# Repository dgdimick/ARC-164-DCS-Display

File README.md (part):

# ARC-164 Radio Panel for DCS

**Last updated: November 14, 2026 at 2:04 AM MST (America/Denver)**

**[Windows COM port tools](Tools/README.md)** — Download the scripts to rename a COM port in Device Manager or restore its previous display name.

*Panel reference photo: PC Flights.*

I’m building an ARC-164 radio panel for my SIMPIT and sharing the files and what I learn along the way. I hope you’ll enjoy building one too, and perhaps help me make it better.

I spend about **8 hours a day on my SIMPIT projects**, including working on the code, PCB design, assembly, and test fitting.

## Development update — November 14, 2026

I finished all three ARC-164 PCB designs and published them as prototypes. The set includes **Main Board v1.2**, **LED Sub Board v1.2**, and **Power Driver Board v1.0**. Next I’ll assemble the manufactured boards and test them electrically. [View the PCB files and downloads](PCBs/README.md).

## Development update — November 10, 2026

**LED Sub Board v1.2 is now published for Main Board v1.2.** I printed the latest mockup at **100%** and it passed the fit test, including **frequency and channel LED alignment and J20 connector/cable clearance**. The final layout keeps the **FREQ LEDs up 0.5 mm**, the **channel LEDs up 0.5 mm with their earlier 0.5 mm leftward adjustment**, and **J20 up 2 mm total** from the previous mounting position. The **0.75 mm gaps, 6 mm display bodies and tested 8 mm mounting stack** remain unchanged. **Use Main Board v1.2 with LED Sub Board v1.2; older Sub Boards do not match this Main Board. Assembled electrical testing is still pending.** [Download the Sub Board v1.2 files and tested STL](PCBs/v1.2/LED-Subboard/README.md).

[Read previous development updates](Docs/Development-Updates.md).

## Physical mockup — November 6, 2026

Here’s my current ARC-164 mockup, showing the faceplate, control shafts, and display covers together with the 3D-printed board assembly. I’m using this to check the mechanical layout and clearances as I continue building the encoder version. This is a physical mockup, not a completed or electrically tested panel. Click the photo to see it full size.

## Power Board images

### Front of the Power Board

Click the image to view it full size.

## Main Board images

### Front of the Main Board

### Back of the Main Board

Click either image to view it full size.

## PCB Sub-Board images

These images show the earlier Sub Board layout, which **does not match Main Board v1.2**. Use the [current Sub Board v1.2 files and tested mockup](PCBs/v1.2/LED-Subboard/README.md) for the matching layout.

### Front of the PCB Sub-Board

### Back of the PCB Sub-Board

Click either image to view it full size.

## Current development order

I’ll **finish the ARC-164 PCBs**, then **take a break from design work and go back to testing the ARC-210**. **The ARC-186 and Version 2 plans can wait.** I haven’t set a date to return to those designs or additional aircraft support.

**This order may change based on user feedback and interest.** These are plans, not fixed release dates.

### Future versions and upgrades

**Future upgrades:** It may be as long as **two years** before I return to this project with upgrades or a new version. Please treat future-version ideas as long-term plans, with no promised release date.

## Other SIMPIT panels

Once I’ve finished the radio panels, I plan to build other panels for my SIMPIT, including the **SAS and emergency trim panels**. I’ll share those projects as they develop. These are future plans.

## Through-hole components

While I could use surface-mount (SMD) parts to make the boards smaller, I plan to use through-hole components to make the project easier for everyone to build and solder with basic tools.

I’ve linked the parts I’m designing around so you can find the same sizes and pin spacing without having to hunt through listings. You’re welcome to use other suppliers—I buy some parts from Amazon myself. Just compare the dimensions and pin spacing before ordering a substitute so it will fit the PCB.

## Recorded component costs

These are my recorded purchases so far, in **US dollars**. The total includes rotary switches bought before I returned to frequency encoders; it is not a shopping list for the current design. The **A11015RNCQ switches are 10-position switches** and were the wrong parts for the ARC-164. **DigiKey did not cancel my order, so I’ll keep the A11015RNCQ switches as parts for ARC-210 V2**.

| Item | Quantity | Cost (USD) |
|---|---:|---:|
| QBSLDIW301GR white seven-segment LED digits — earlier purchase; superseded by SC36-11SURKWA in the current build plan | 10 | $17.43 |
| A12515RNCQ rotary switches — earlier long-shaft selection; no longer the current MAIN/PRESET choice | 5 | $55.66 |
| A11015RNCQ rotary switches — 10 positions; DigiKey order not canceled, retained for ARC-210 V2 | 3 | $35.07 |
| Tax and tariffs on the rotary-switch and LED order | — | $27.13 |
| Toggle-switch purchase | — | $13.51 |
| Toggle-switch purchase | — | $10.76 |
| Faceplate | 1 | $57.00 |
| Faceplate shipping | — | $13.59 |
| Pushbutton switches | — | $7.99 |
| Teensy 4.1 | 1 | $29.60 |
| Teensy shipping | — | $8.35 |
| **Running total** | | **$276.09** |

My Teensy 4.1 cost **$37.95 including shipping**, and my faceplate cost **$70.59 including shipping**. The rotary switches and LEDs came to **$108.16**, or **$135.29 including tax and tariffs**. Those charges are already included in the running total. I bought two spare LED digits and one spare A12515RNCQ switch because the quantity price breaks saved me money compared with buying only the quantities I originally planned to use. I still need to verify the selected toggle switches’ fit and operation.

I’m keeping the extra displays I bought as spares, since returning them would only get me **US$2.77** back.

**The VOL encoder isn’t included in the total yet.** My current selection for VOL, FREQ, and channel is **PEC11R-4230F-S0024 with a 30 mm shaft**, sourced from Mouser. I’ll add actual encoder costs to this purchase history once the order is confirmed.

**This total is before PCBs, display drivers, resistors, connectors, and the other remaining parts. It is not the complete build cost.** I’ll update the total as I buy the remaining parts. Additional shipping or fees not listed above are also excluded.

## Order sheet — rotary controls and LED digits

**Current build: rotary encoders.** I’ll finish the current ARC-164 PCBs, then take a break from design work and return to testing the ARC-210. The ARC-186 and Version 2 rotary-switch plans are deferred; PC Flights has confirmed the larger-hole panel is available on request when I’m ready for it. The order sheet below is for the encoder version; quantities and fit still need final checks before purchasing.

This is my order sheet for **one ARC-164 panel**, updated **November 4, 2026**. I’ll buy the **30 mm encoders and SC36-11SURKWA LED digits from Mouser**. The MAIN and PRESET switches remain on the DigiKey list. These are full build quantities; I’ll deduct parts I already have before ordering.

| Quantity | Use | Manufacturer part number | Supplier / order number | Estimated unit price (USD) | Estimated total (USD) |
| ---: | --- | --- | --- | ---: | ---: |
| 7 | Five FREQ encoders, channel encoder, and VOL | PEC11R-4230F-S0024 | [Mouser: 652-PEC11R-4230F-S24](https://www.mouser.com/en/ProductDetail/Bourns/PEC11R-4230F-S0024?qs=Zq5ylnUbLm6MC5h%2FLr6Brg%3D%3D) | $2.07 | $14.49 |
| 2 | MAIN and PRESET rotary switches | A12505RNCQ | [DigiKey: CKN10203-ND](https://www.digikey.com/en/products/detail/c-k/A12505RNCQ/2043159) | $13.41 | $26.82 |
| 10 | Red 0.36-inch common-cathode seven-segment LED digits | SC36-11SURKWA | [Mouser: 604-SC36-11SURKWA](https://www.mouser.com/en/ProductDetail/Kingbright/SC36-11SURKWA?qs=FRBiz4Wv1YMkVf5BvlPtDA%3D%3D) | $1.45 | $14.50 |
| | **Estimated subtotal** | | | | **$55.81** |

All seven encoders have **30 mm shafts**. MAIN and PRESET use the **same A12505RNCQ switch**, with the stop ring set to **4 positions for MAIN** and **3 positions for PRESET**; both index at **45° per position**.

This earlier estimate uses the quantity-five encoder tier, quantity-one switch tier, and Mouser’s quantity-ten SC36-11SURKWA LED tier; it has not yet been recalculated for my purchased white displays. The LED price is $1.45 each ($14.50 for ten), checked November 4, 2026. Prices can change; shipping, tax, and tariffs are excluded. This estimate is separate from my recorded purchases.

**This is not the complete build BOM.** TONE, SQL, STATUS, display drivers, other display components, resistors, capacitors, connectors, PCBs, and other remaining parts are excluded.

### Recommended IC sockets and Teensy headers

**I normally recommend using sockets for the DIP ICs and a removable header/socket connection for the Teensy.** This reduces the risk of overheating the ICs when soldering and makes replacement easier. Solder the empty sockets to the PCB first, let the board cool, and then insert the ICs with their pin-1 notches facing the correct way.

| Quantity | Use | Manufacturer part number | Mouser order number / link |
| ---: | --- | --- | --- |
| 2 | 24-pin DIP sockets for the MAX7219 drivers, U11 and U12; 7.62 mm row spacing, 2.54 mm pin pitch | TE Connectivity 1-2199298-8 | [571-1-2199298-8](https://www.mouser.com/ProductDetail/TE-Connectivity/1-2199298-8?qs=fK8dlpkaUMsSY7Gqcrol0Q%3D%3D) |
| 1 | 14-pin DIP socket for the 74AHCT125 buffer, U13; 7.62 mm row spacing, 2.54 mm pin pitch | TE Connectivity 1-2199298-3 | [571-1-2199298-3](https://www.mouser.com/en/ProductDetail/TE-Connectivity/1-2199298-3?qs=fK8dlpkaUMtBOtVI99wRlQ%3D%3D) |
| 2 | Single-row 24-pin male headers for the Teensy 4.1's two outer rows; 2.54 mm pitch | Samtec TSW-124-07-T-S | [200-TSW12407TS](https://www.mouser.com/en/ProductDetail/Samtec/TSW-124-07-T-S?qs=rU5fayqh%252BE26VY6qw728rQ%3D%3D) |
| 2 | Matching single-row 24-pin female sockets on the Power Driver Board; 2.54 mm pitch | Samtec SSW-124-01-T-S | [200-SSW12401TS](https://www.mouser.com/ProductDetail/Samtec/SSW-124-01-T-S?qs=iT52DjcXudvCUishYlzKnw%3D%3D) |

All of these parts are through-hole and can be hand soldered. The Teensy still needs its male headers soldered on unless you buy it with pins already fitted; use a temperature-controlled iron and avoid prolonged heating. The female sockets let you unplug the complete Teensy module from the Power Driver Board. Check the added socket/header height when setting the clearance to the board above it. These items are separate from the rotary-control and LED subtotal; check current supplier pricing.

### External regulated 5 V power supply

| Quantity | Use | Manufacturer part number | Supplier / order number |
| ---: | --- | --- | --- |
| 1 | J11 edge-mounted, right-angle, through-hole barrel power jack | Same Sky PJ-102AH | [Mouser: 490-PJ-102AH](https://www.mouser.com/en/ProductDetail/Same-Sky/PJ-102AH?qs=WyjlAZoYn50Yq4CrVLCXLw%3D%3D) |
| 1 | Regulated 5 V, 4 A supply for the displays and panel backlighting | MEAN WELL GST25A05-P1J | [Mouser: 709-GST25A05-P1J](https://www.mouser.com/en/ProductDetail/MEAN-WELL/GST25A05-P1J?mgh=1&qs=drgMNd%252BkGPOX8brSXUPVtQ%3D%3D) |

**You can use another power supply, but it must provide well-regulated 5 V DC**, with a voltage tolerance of **±5% or better**, enough current for the connected panels, and a **5.5 mm outer / 2.1 mm inner, center-positive barrel plug** to fit J11. The recommended supply provides 4 A; the circuit draws only the current it needs. The Power Driver Board does not reduce a higher input voltage to 5 V.

The GST25A05-P1J requires a separate **IEC C13 mains cord** (the standard desktop-computer type). See the [MEAN WELL datasheet](https://www.meanwell.com/Upload/PDF/GST25A/GST25A-SPEC.PDF). The Teensy remains powered through USB; the external supply powers the display and backlight circuits. The jack, supply, and mains cord are **not included in the rotary-control and LED subtotal above**; check current supplier pricing.

### USB adapter cable

Use **one USB-C-to-Micro-B data cable per panel** to connect the Teensy 4.1’s Micro-B device port to a computer or hub with a USB-C port. The linked option is a **1 ft (30.5 cm), male-to-male cable carrying both data and power**:

[Amazon — USB-C-to-Micro-B adapter cable](https://www.amazon.com/dp/B0BD36TZBK)

This replaces the standard USB Micro-B data cable when using a USB-C port; you only need one suitable USB data cable per panel. A charge-only cable will not carry DCS-BIOS communications or program the Teensy. Choose a length that suits your installation and check the current supplier price.

The USB cable is separate from the rotary-control and LED subtotal above; its cost has not been added to the recorded purchase history.

### Additional Mouser items — green panel backlighting

I’ve selected **Kingbright WP710A10SGD**, a **3 mm through-hole green LED with a diffused lens**, for the ARC-164 and ARC-210 panel-backlighting plan. See [Mouser part 604-WP710A10SGD](https://www.mouser.com/ProductDetail/Kingbright/WP710A10SGD?qs=jBF9H7RTBaS5vBvRdVQZww%3D%3D) and the [Kingbright datasheet](https://www.kingbrightusa.com/images/catalog/spec/wp710a10sgd.pdf). Final brightness, light spread, and mounting fit behind the lettering still need testing.

**Backlight LED quantities are still being decided.** The figures below are provisional planning estimates, not finalized purchase quantities. I’ll confirm them after laying out the LEDs behind the lettering and testing light coverage.

| Provisional quantity | Allocation | Manufacturer part number | Mouser order number |
| ---: | --- | --- | --- |
| 19 | ARC-164 Version 1.0 prototype backlighting | WP710A10SGD | 604-WP710A10SGD |
| 38 | ARC-210 backlighting | WP710A10SGD | 604-WP710A10SGD |
| **57 total** | **Planning total only; final quantity TBD, excluding spares** | **WP710A10SGD** | **604-WP710A10SGD** |

These LEDs require **one current-limiting resistor per LED branch** on the regulated 5 V supply. I’ll start brightness testing with **330 Ω resistors**, approximately **8.5 mA per LED** at the datasheet’s typical 2.2 V forward voltage; actual current and brightness will vary. For the provisional 57-LED combined estimate, that nominal current would draw approximately 0.48 A at full duty, excluding the displays and controllers. The final resistor selection and power budget remain subject to testing.

The LEDs will sit behind the lettering, with opaque shielding around display windows. They will use the panel-backlighting driver, not the MAX7219 segment outputs. **Confirm price and availability in the Mouser cart; these additional LEDs and their resistors are not included in the $55.81 ARC-164 subtotal above.**

### Additional item for my Mouser order — emergency trim panel

I’ll add this part to the same Mouser order as the ARC-164 encoders. It is for my **A-10 emergency pitch/roll trim panel**, not the ARC-164 radio.

| Quantity | Use | Manufacturer part number | Mouser order number | Estimated cost (USD) |
| ---: | --- | --- | --- | --- |
| 1 | Emergency pitch/roll trim directional switch | Alps Alpine RKJXT1F42001 | [688-RKJXT1F42001](https://www.mouser.com/en/ProductDetail/Alps-Alpine/RKJXT1F42001?qs=6EGMNY9ZYDTsBzSTrhiL0w%3D%3D) | Confirm USD price in cart |

This is a **four-direction switch with a center pushbutton and rotary encoder**. I plan to use its four directions for emergency pitch and roll trim; the center pushbutton and rotary encoder will remain unused. Physical mounting, knob fit, and operating feel still need checking. Its cost is **not included in the $55.81 ARC-164 subtotal** above.

## 3D print settings

Use a **0.20 mm or finer layer height**. Print the knobs **without supports** in their intended orientation.

The rotary encoder shaft adapters will be hidden. Black filament is preferred if you have it available.

## Free 3D-printed parts

If you don’t have a 3D printer, I’m happy to help with the ARC-164. Once the printed parts are finalized, I’ll print a set for you for free. Just cover shipping. I’m still designing and test-fitting some of the printed parts. If you’re planning a build, [get in touch in Discussions](https://github.com/dgdimick/ARC-164-DCS-Display/discussions) to check availability.

## Things that need to be completed

**Last updated: November 11, 2026 at 10:50 PM MST (America/Denver)**
<!-- Refresh this section timestamp whenever the work list changes, using the actual America/Denver time and MST/MDT. -->

This is my current work list for the hardware, firmware, testing, and build instructions.

1. **Panel layout and parts:** Confirm dimensions, mounting clearances, controls, and the complete parts list. **TONE and SQL switches:** Select the exact parts and verify their mounting dimensions, required operation and travel, and clearances before finalizing the PCB. My purchased **QBSLDIW301GR white digits—six for frequency and two for channel—have passed the printed layout fit test**. The revised six-digit frequency layout is **49.35 mm wide × 13.75 mm high across the front face**, using **0.75 mm gaps**. The earlier LED layout mockup passed at 100% scale; the matching **Sub Board v1.2 has now passed its latest frequency/channel LED alignment and J20 clearance fit checks and is published**. Verify the prototype LED Sub-Board footprint and pinout against these displays before assembly. Check digit visibility and brightness through the smoked covers, pinout, mounting height, spacing, and clearance within the 53.5 × 17.5 mm frequency window and 22 × 17.5 mm preset window.
2. **Assemble and electrically test the matched v1.2 boards:** The **LED Sub Board v1.2 mockup passed its 100% print and fit test on November 10, 2026**, including frequency/channel LED alignment and J20 connector/cable clearance with Main Board v1.2. Both boards are published. Verify the manufactured boards, connector/cable fit, power, display pinout, controls and assembled electrical operation before calling the complete panel tested. Keep the current frequency-encoder design; I’ll finish these PCBs and return to ARC-210 testing before revisiting ARC-186 or Version 2.
3. **Printed parts:** The **8 mm Sub Board mounting stack** and **latest v1.2 display-board mockup** have passed physical fit testing at **100% scale**, including both display windows and J20 clearance. Continue designing and test-fitting the remaining knobs, brackets and spacers; verify shaft engagement, knob retention and their clearances. Design and test-fit shaft adapters for the rotary encoders.
4. **DCS-BIOS mappings and any needed changes:** Check which inputs and display outputs are already available for this radio. Identify missing data, make any necessary export changes, and document them. Check the correct ARC-164 radio instance for each intended A-10 variant.
5. **Firmware:** Write the control and display firmware and verify USB communication with DCS-BIOS. Implement DCS-BIOS-controlled MAX7219 display brightness and PWM panel backlighting, with separate brightness curves and off-state handling; see the [lighting design plan](#dcs-bios-display-brightness-and-panel-backlighting).
6. **Bench and board testing:** Test the controls, displays, and power requirements together, then assemble and electrically test the manufactured boards.
7. **Dual ARC-164 support:** For aircraft with two ARC-164 radios, such as the A-10C, I’ll provide two separate HEX files, one for **Radio 1** and one for **Radio 2**. Load the HEX file that matches the radio you want each physical panel to control. The Teensy will report **ARC-164-1** or **ARC-164-2** as its USB product name in **Device Manager → Properties → Details → Bus reported device description**, depending on the HEX file you load. Windows may still show a generic COM-port label in Device Manager. I’ll verify the DCS-BIOS mappings for both radio instances and test both panels together.
8. **Testing in DCS:** Check control operation, display updates, startup behavior, reconnection, and extended reliability with the intended aircraft and the other radio panels connected.
9. **Documentation:** Publish assembly instructions, wiring diagrams, final parts and print quantities, PCB ordering files, firmware loading steps, DCS-BIOS setup requirements, and troubleshooting notes.
10. **Assembly pictures:** During assembly, take clear pictures of component placement, soldering, wiring, and mounting, including both sides of each PCB with the silkscreen markings visible. Add the pictures to the assembly instructions so other builders can follow along.
11. **USB-C adapter testing:** I confirmed DCSBridge panel control and Teensy programming on my ARC-210. I still need to check live DCS operation and reliable reconnection after unplugging the adapter.
12. **USB identification:** Verify the USB product names **ARC-164-1** and **ARC-164-2** with their respective HEX files. Test and document the optional Windows Ports label change using administrator permissions. The panel can be programmed and used with DCS-BIOS without that registry change. [ARC-210 Windows naming example](https://github.com/dgdimick/ARC-210-DCS-Display#arc-210-usb-name-in-windows).

## Controller choice — Teensy 4.1

I’m using the **Teensy 4.1** for its compact size and room for the panel’s controls and displays. It runs at **600 MHz**, compared with **16 MHz for the classic Arduino Uno R3, Mega 2560, and ATmega328P Nano**. I still need to finalize the pin assignments. See the [Teensy specifications](https://www.pjrc.com/store/teensy41.html).

I’ll use USB for DCS-BIOS; Ethernet isn’t needed. The Teensy uses **3.3 V logic**, and its inputs are **not 5 V tolerant**, so I’ll design the display-driver connections accordingly.

## Seven-segment display plan

My **QBSLDIW301GR white single-digit seven-segment displays** from [DigiKey, part 1516-QBSLDIW301GR-ND](https://www.digikey.com/en/products/detail/qt-brightek-qtb/QBSLDIW301GR/22077720), have arrived. I bought **10: six for frequency, two for channel, and two spares**. These are my current display selection, replacing the earlier red Kingbright and amber PC Flights plans.

I measured each display body at **7.6 mm wide × 13.75 mm high across the front face, with a 6 mm body height above the PCB**. These are body measurements, rather than illuminated-digit dimensions. I still need to verify the prototype LED Sub-Board footprint and pinout against the actual displays before assembly.

### Frequency display

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
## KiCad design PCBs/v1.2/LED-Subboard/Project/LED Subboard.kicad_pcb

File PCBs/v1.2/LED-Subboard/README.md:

# ARC-164 LED Sub Board — Version 1.2

**Last updated: November 10, 2026 at 5:45 PM MST (America/Denver)**

**LED Sub Board v1.2 is now published for Main Board v1.2.** I printed the latest mockup at **100%** and it passed the fit test, including **frequency and channel LED alignment and J20 connector/cable clearance**. The final layout keeps the **FREQ LEDs up 0.5 mm**, the **channel LEDs up 0.5 mm with their earlier 0.5 mm leftward adjustment**, and **J20 up 2 mm total** from the previous mounting position. The **0.75 mm gaps, 6 mm display bodies and tested 8 mm mounting stack** remain unchanged. **Use Main Board v1.2 with LED Sub Board v1.2; older Sub Boards do not match this Main Board. Assembled electrical testing is still pending.**

## Downloads

- [Complete LED Sub Board v1.2 package](LED-Subboard-v1.2.zip)
- [KiCad project](Project/LED%20Subboard.kicad_pro)
- [Schematic PDF](Schematics/LED-Subboard-v1.2.pdf)
- [Component BOM](Assembly/BOM.csv)
- [Gerber and drill ZIP](LED-Subboard-v1.2-Gerbers.zip)
- [Exact fit-tested STL — print at 100%](STLs/ARC-164_LED_Subboard_v1.2_100pct.stl)
- [DRC and schematic parity report](Checks/DRC.rpt) · [ERC report](Checks/ERC.rpt)

## Displays and mounting

I use **eight QBSLDIW301GR white common-cathode digits**: six for frequency and two for channel. Each measured body is **7.6 mm wide × 13.75 mm front-face height × 6 mm deep**. With **0.75 mm gaps**, the frequency group spans **49.35 mm** and the channel pair spans **15.95 mm**.

The Sub Board mounts above **Main Board v1.2**, using four mounts, each with a **20 mm screw, 6 mm-thick nut and two 1 mm washers**, giving **8 mm spacing**. J20's cable connector clearance passed the printed mockup fit test. The footprint still represents the current vertical 40-pin header; the earlier right-angle adapter idea is not a change to this PCB footprint.

Panel-to-Main-Board spacing is currently **13.5 mm**; I may use **14 mm** after checking the manufactured PCBs. The Power Driver Board remains at **v1.0 Prototype**, below Main with its components facing down, on **10 standoffs longer than 20 mm**.

[Assembly instructions](../../v1.0-Prototype/Docs/Assembly.md) · [Wiring and J20 pinout](../../v1.0-Prototype/Docs/Wiring.md) · [Main Board v1.2](../Main-Board/README.md)

## Validation

Fresh KiCad checks report **zero DRC violations, zero unconnected items, zero schematic parity issues and zero ERC violations under the saved project settings**. The reports list checks that remain disabled. The generic display STEP is a measured-body clearance box, not a detailed manufacturer model.

The successful 100% printed fit test checks mechanical placement and connector clearance. I still need to assemble the manufactured boards and check display pinout, segment order, brightness, power and electrical operation. This is not yet an electrically validated complete radio.

## Version history

- **1.2 — November 10, 2026:** Resized Sub Board, final display placement and J20 position; latest 100% print and physical fit test passed. Published for use with Main Board v1.2.
- **1.1 — November 8, 2026:** Earlier layout, subsequently withdrawn during the J20 clearance redesign.
- **1.0 Prototype — November 7, 2026:** Initial prototype, withdrawn.

[Current PCB versions](../../README.md)

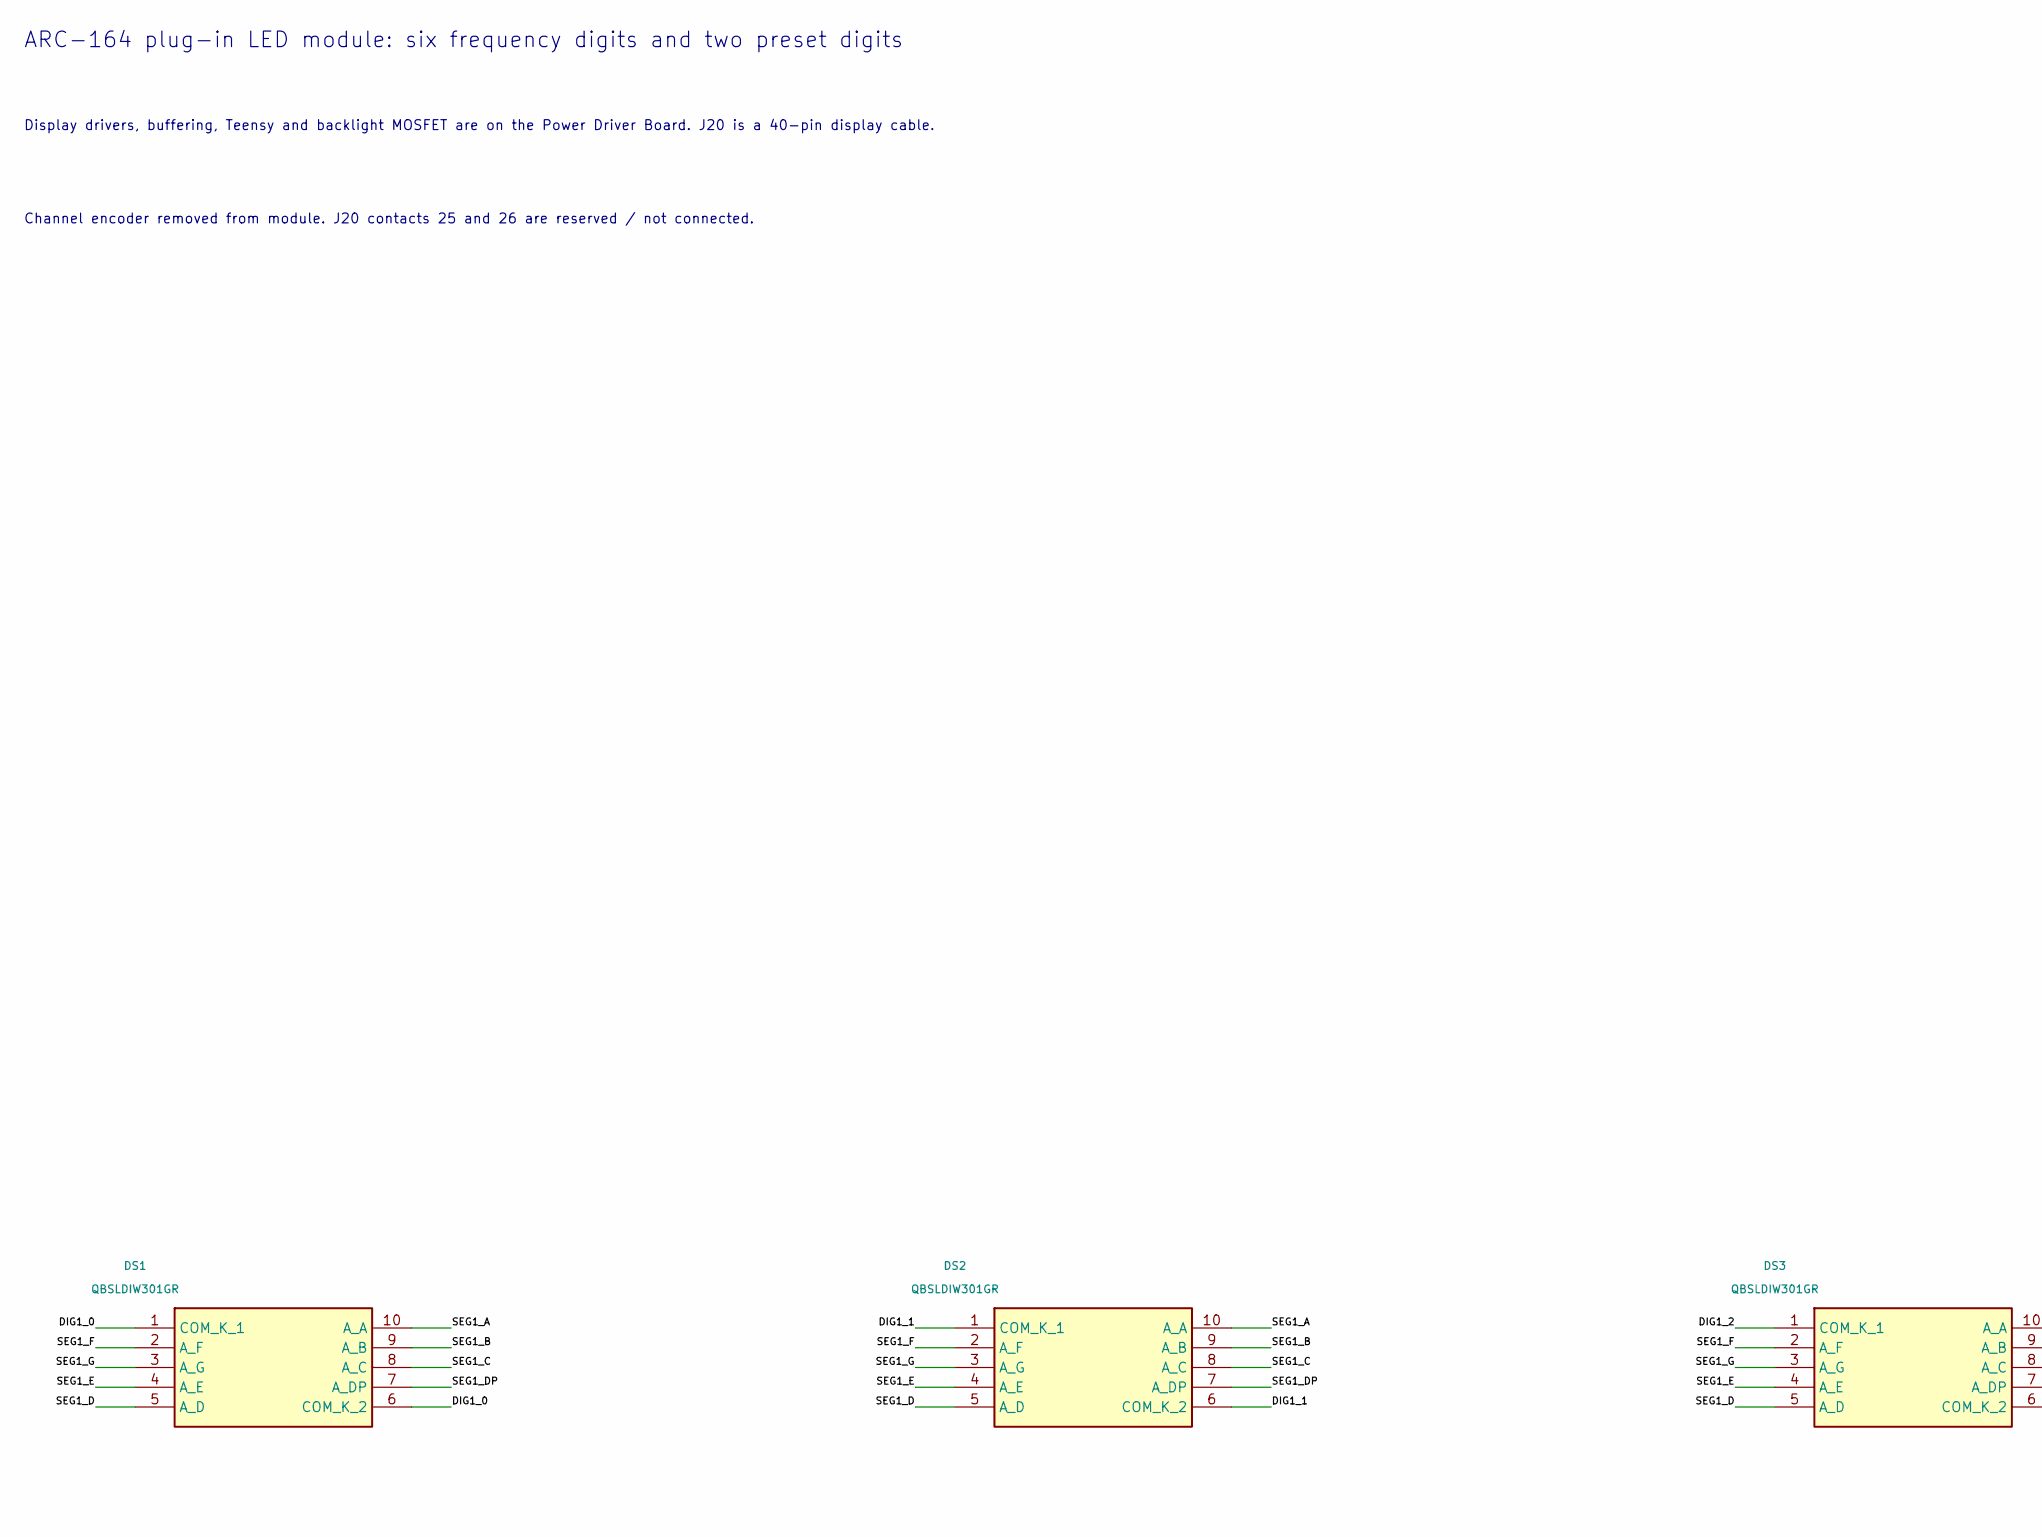
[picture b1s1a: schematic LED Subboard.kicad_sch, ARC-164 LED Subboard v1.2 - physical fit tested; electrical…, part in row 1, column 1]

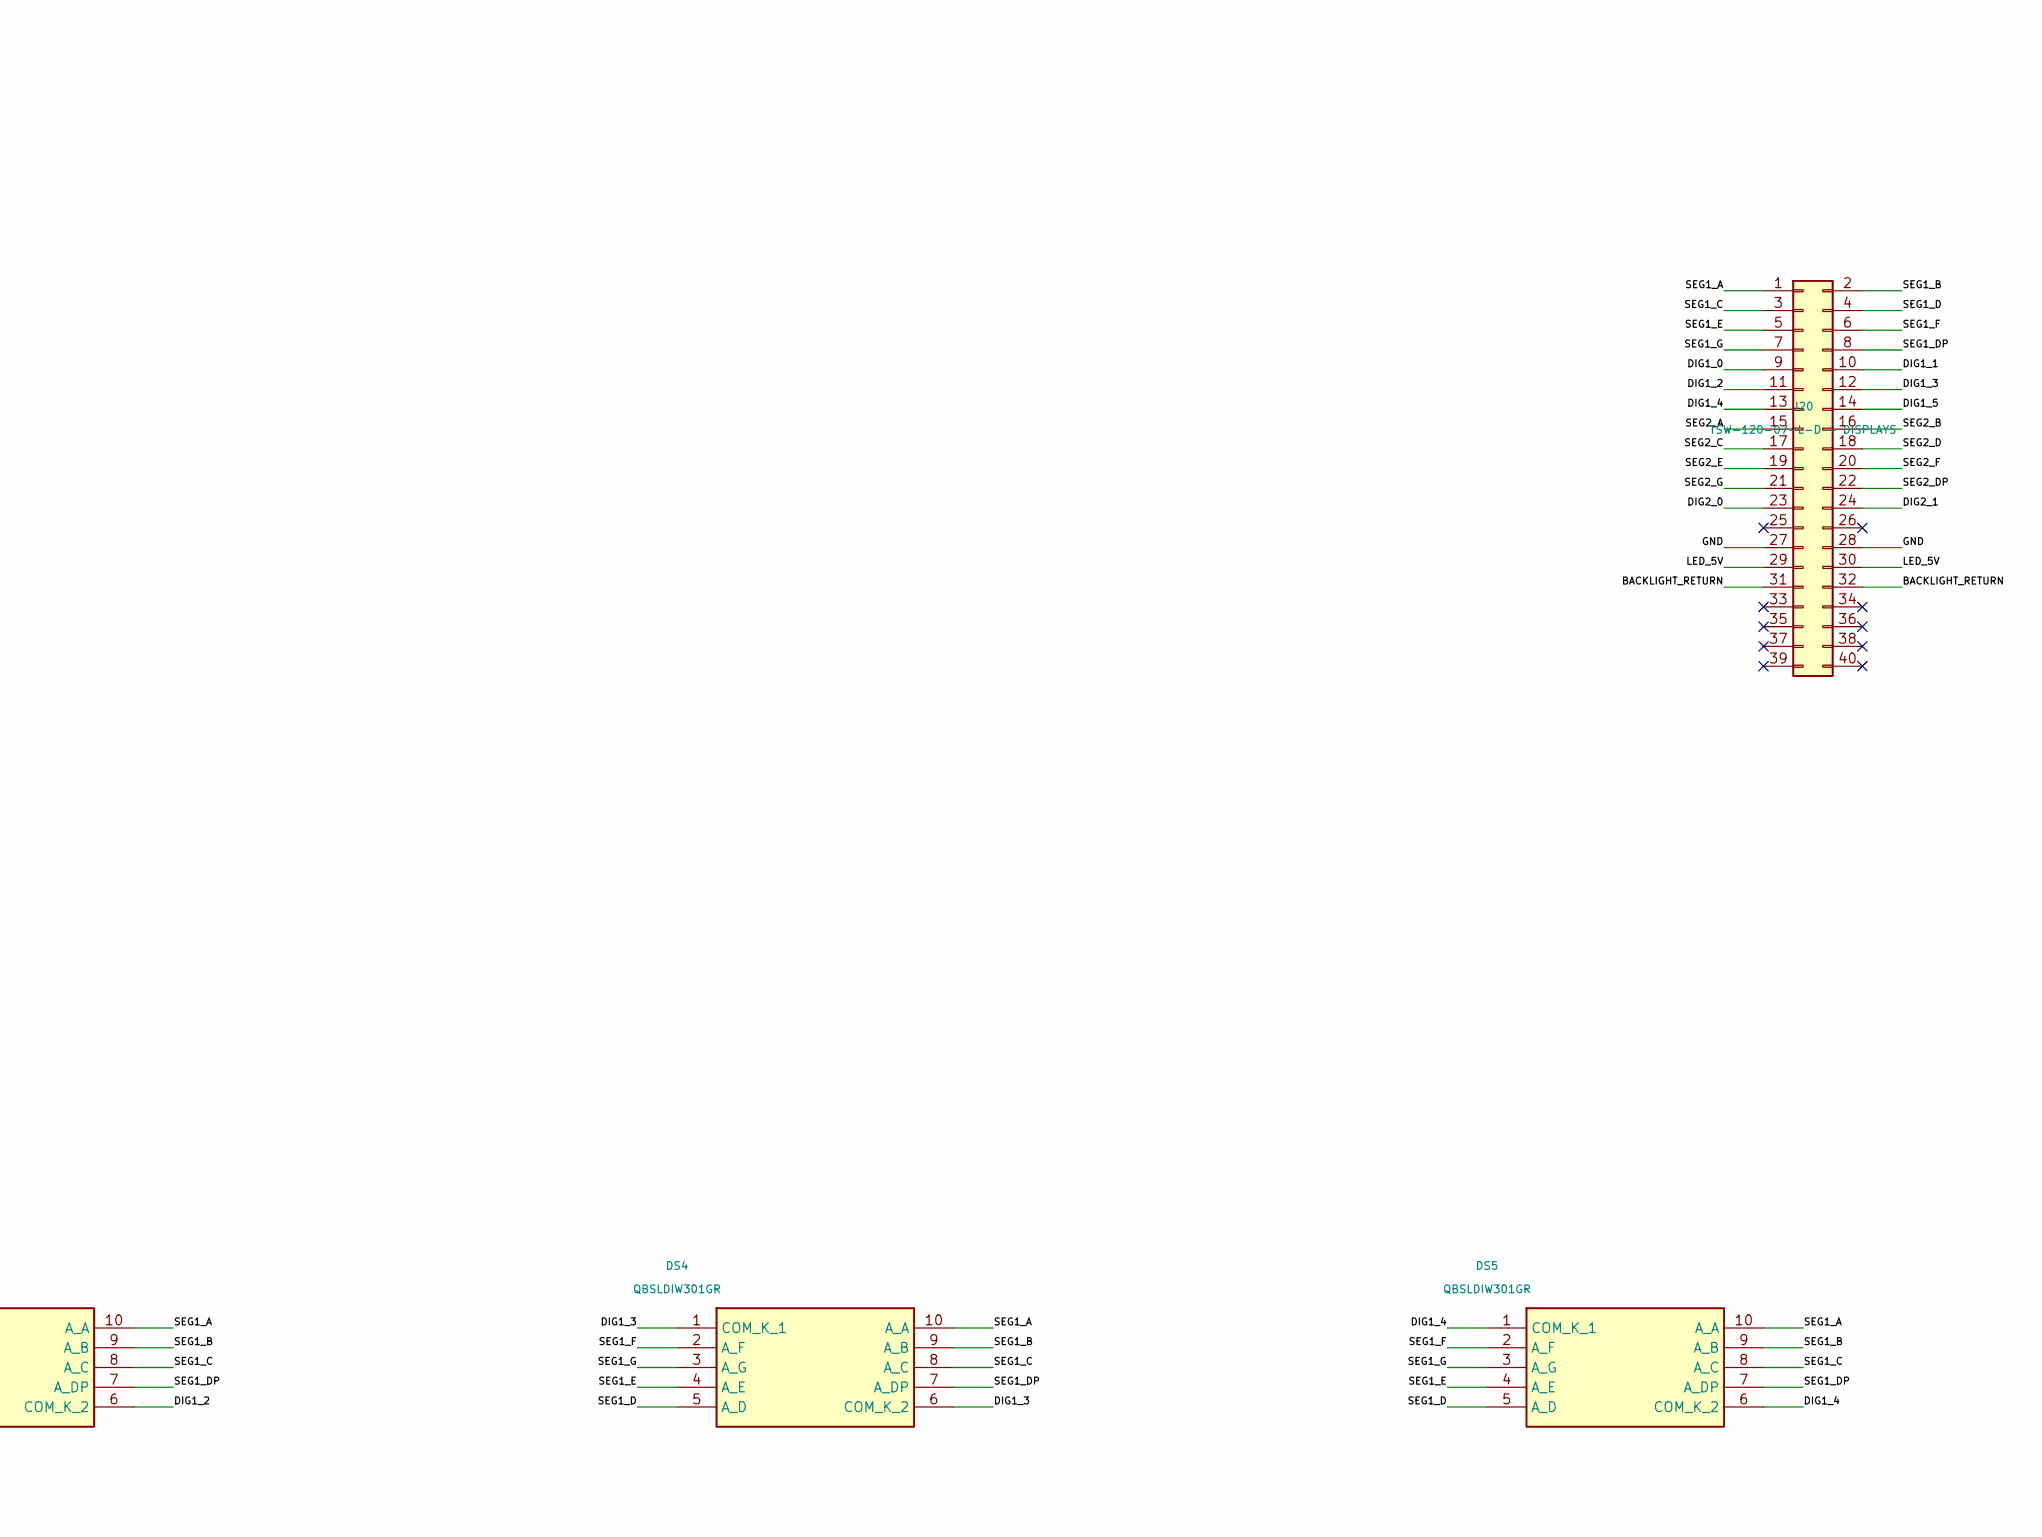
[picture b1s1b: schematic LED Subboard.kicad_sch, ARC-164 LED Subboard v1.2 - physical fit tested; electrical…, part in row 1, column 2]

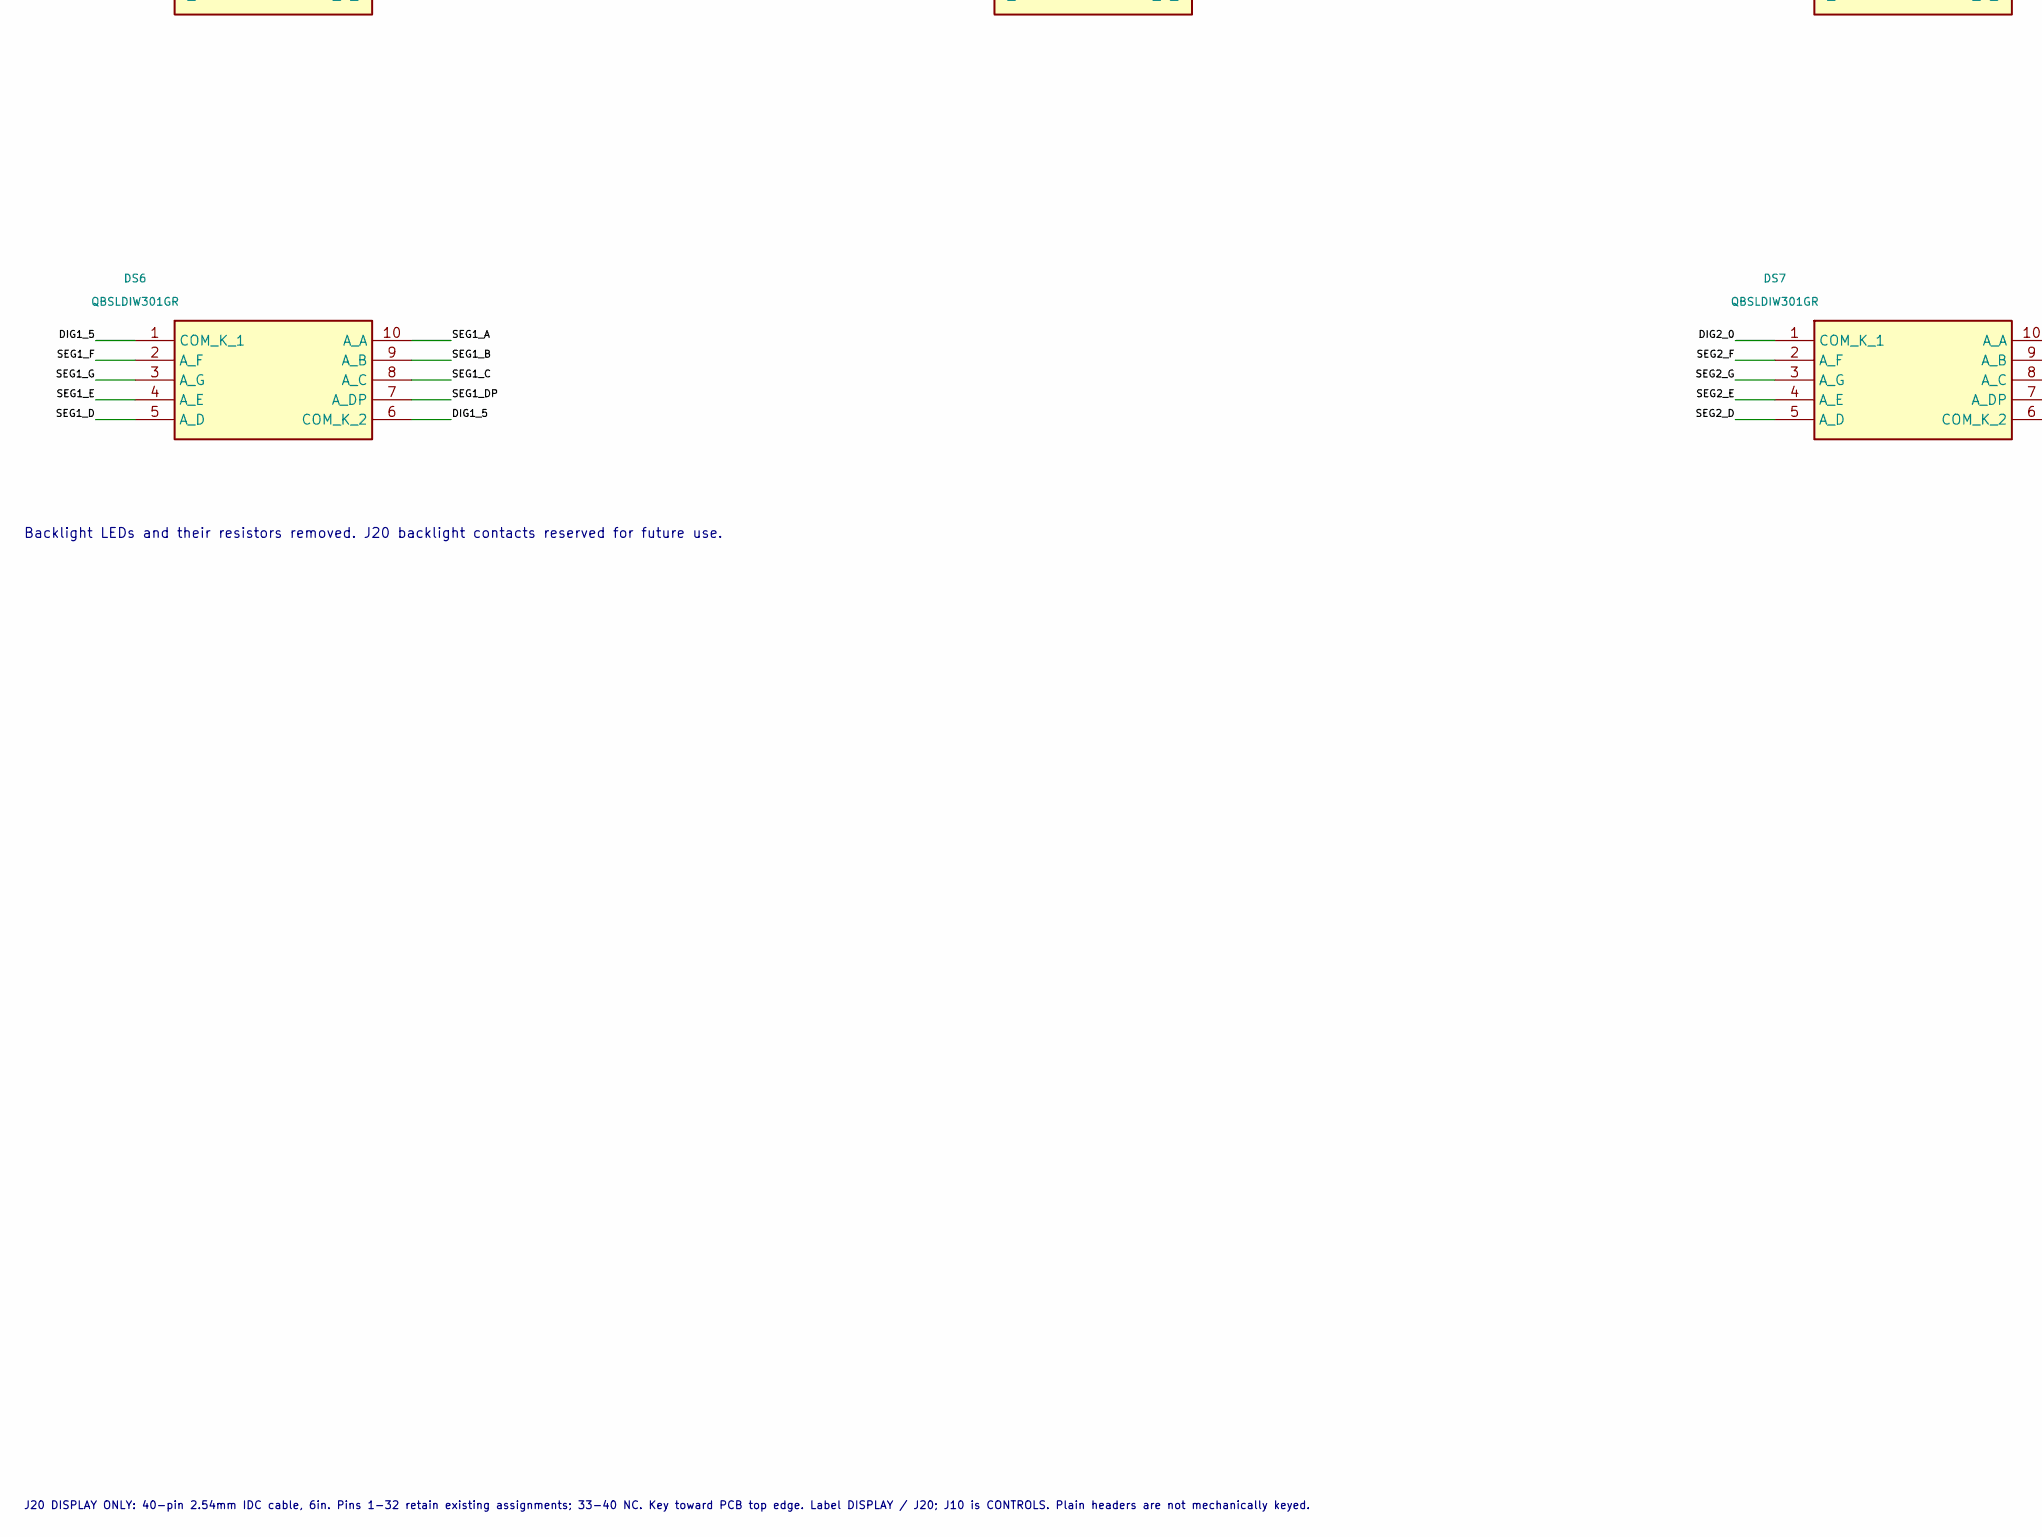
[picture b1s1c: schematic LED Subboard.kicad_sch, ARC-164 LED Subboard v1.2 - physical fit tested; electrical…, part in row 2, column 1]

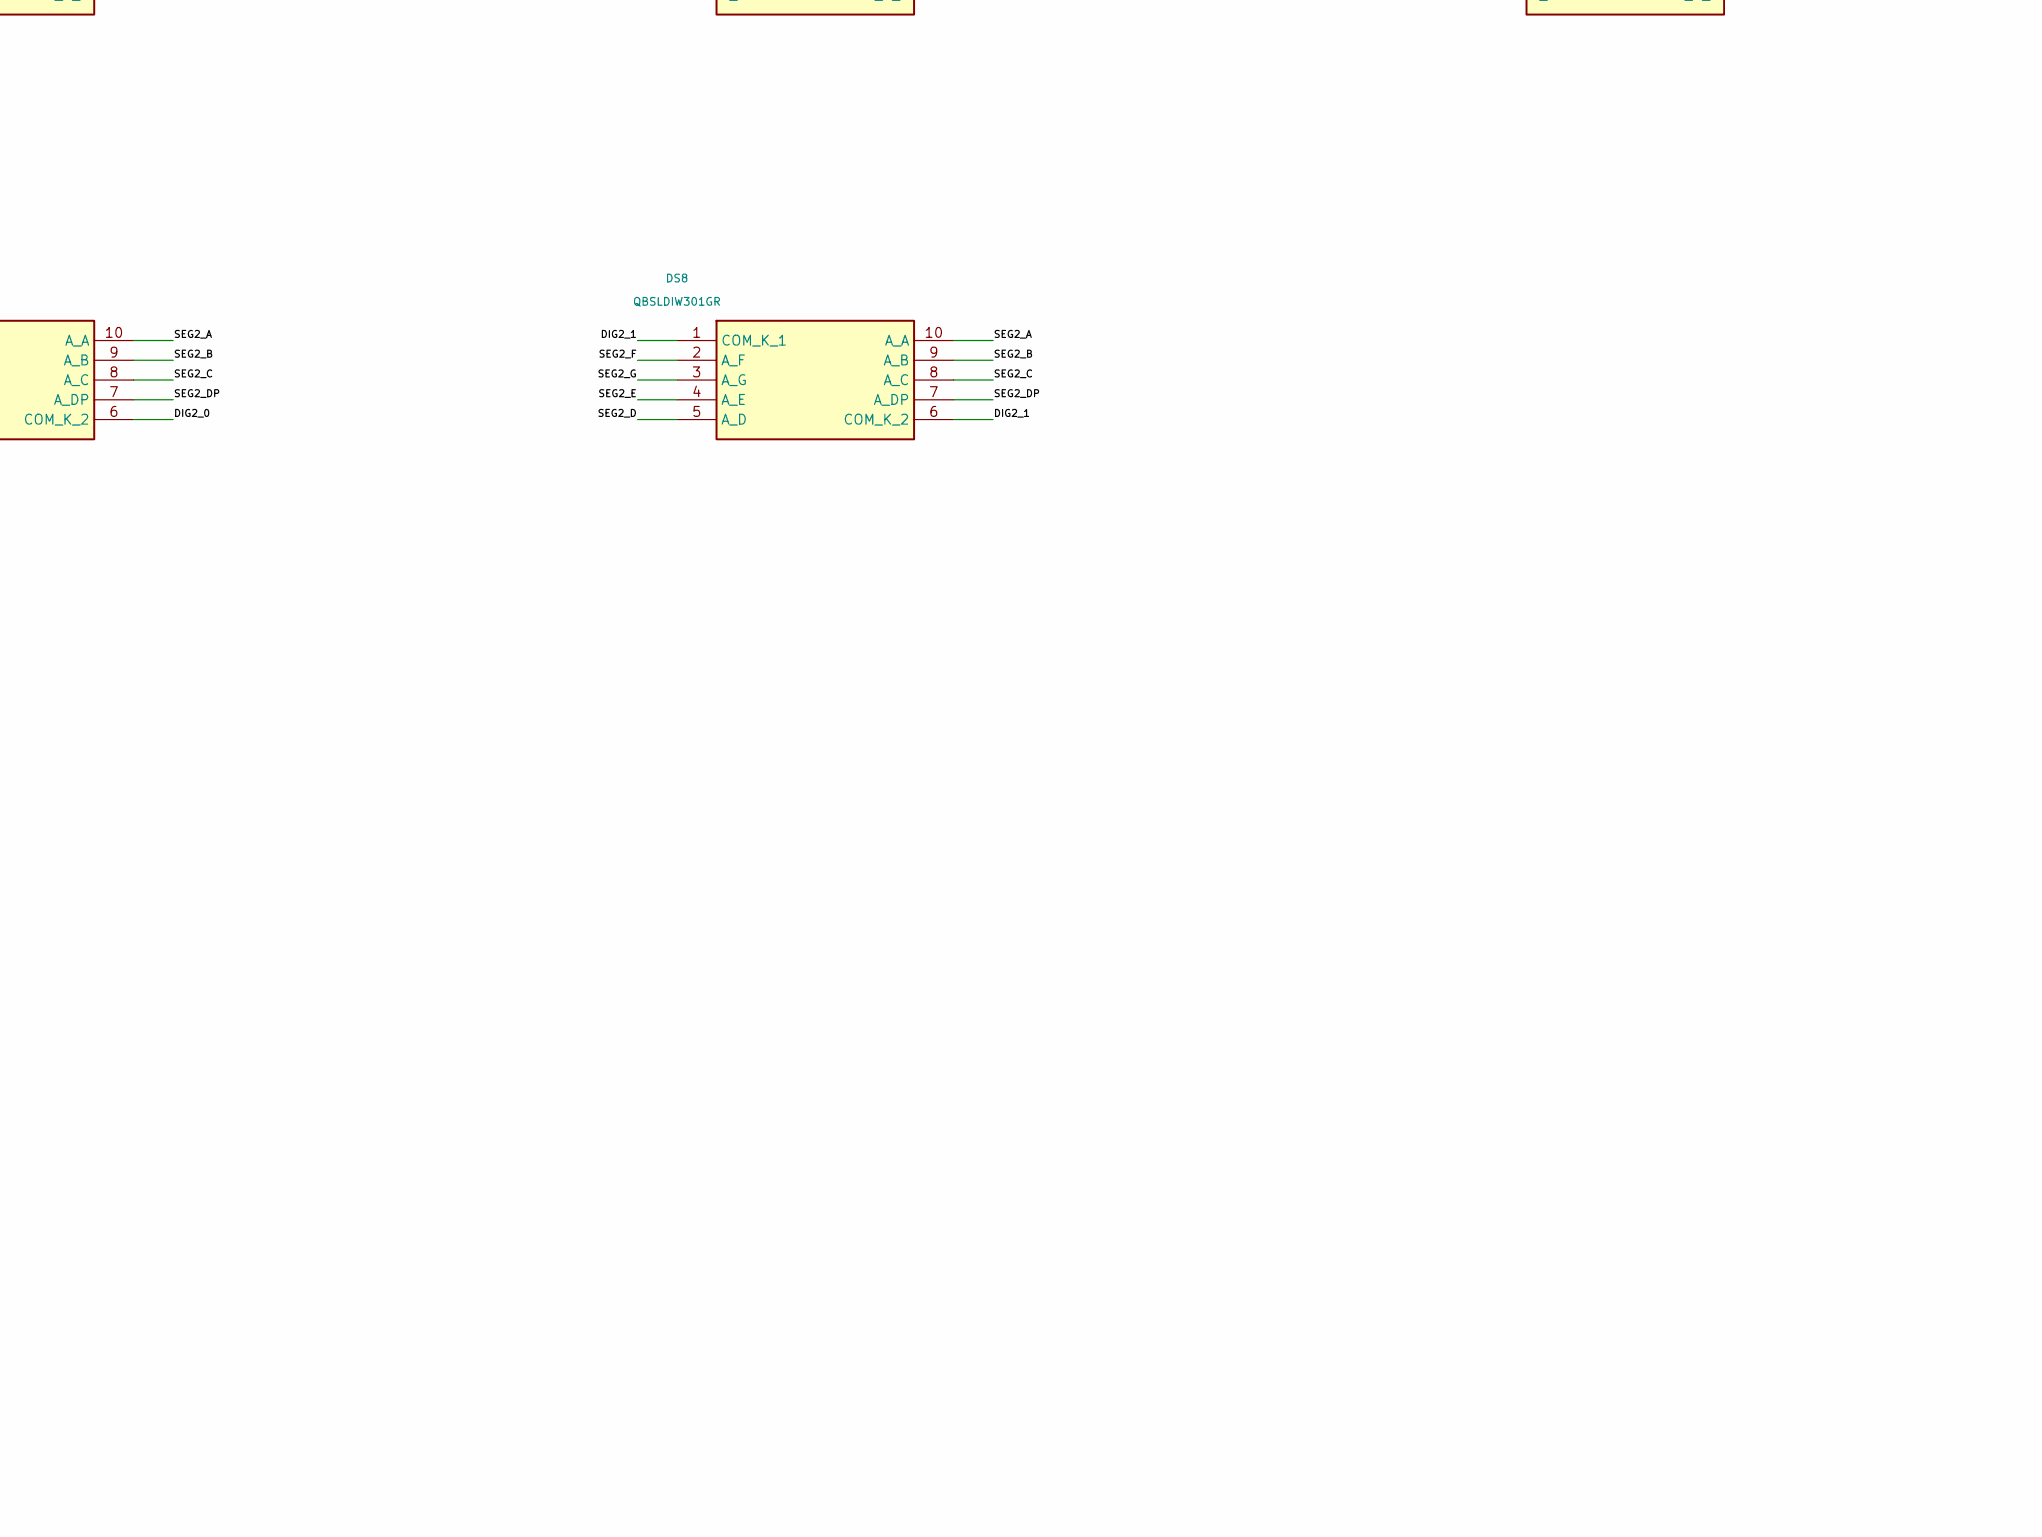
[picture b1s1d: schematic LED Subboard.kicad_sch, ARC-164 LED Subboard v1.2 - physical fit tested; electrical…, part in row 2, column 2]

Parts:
DS1, DS2, DS3, DS4, DS5, DS6, DS7, DS8: QBSLDIW301GR
J20: TSW-120-07-L-D - DISPLAYS; PinHeader_2x20_P2.54mm_Vertical

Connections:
/BACKLIGHT_RETURN: J20.31, J20.32
/DIG1_0: DS1.1 (COM_K_1), DS1.6 (COM_K_2), J20.9
/DIG1_1: DS2.1 (COM_K_1), DS2.6 (COM_K_2), J20.10
/DIG1_2: DS3.1 (COM_K_1), DS3.6 (COM_K_2), J20.11
/DIG1_3: DS4.1 (COM_K_1), DS4.6 (COM_K_2), J20.12
/DIG1_4: DS5.1 (COM_K_1), DS5.6 (COM_K_2), J20.13
/DIG1_5: DS6.1 (COM_K_1), DS6.6 (COM_K_2), J20.14
/DIG2_0: DS7.1 (COM_K_1), DS7.6 (COM_K_2), J20.23
/DIG2_1: DS8.1 (COM_K_1), DS8.6 (COM_K_2), J20.24
/GND: J20.27, J20.28
/LED_5V: J20.29, J20.30
/SEG1_A: DS1.10 (A_A), DS2.10 (A_A), DS3.10 (A_A), DS4.10 (A_A), DS5.10 (A_A), DS6.10 (A_A), J20.1
/SEG1_B: DS1.9 (A_B), DS2.9 (A_B), DS3.9 (A_B), DS4.9 (A_B), DS5.9 (A_B), DS6.9 (A_B), J20.2
/SEG1_C: DS1.8 (A_C), DS2.8 (A_C), DS3.8 (A_C), DS4.8 (A_C), DS5.8 (A_C), DS6.8 (A_C), J20.3
/SEG1_D: DS1.5 (A_D), DS2.5 (A_D), DS3.5 (A_D), DS4.5 (A_D), DS5.5 (A_D), DS6.5 (A_D), J20.4
/SEG1_DP: DS1.7 (A_DP), DS2.7 (A_DP), DS3.7 (A_DP), DS4.7 (A_DP), DS5.7 (A_DP), DS6.7 (A_DP), J20.8
/SEG1_E: DS1.4 (A_E), DS2.4 (A_E), DS3.4 (A_E), DS4.4 (A_E), DS5.4 (A_E), DS6.4 (A_E), J20.5
/SEG1_F: DS1.2 (A_F), DS2.2 (A_F), DS3.2 (A_F), DS4.2 (A_F), DS5.2 (A_F), DS6.2 (A_F), J20.6
/SEG1_G: DS1.3 (A_G), DS2.3 (A_G), DS3.3 (A_G), DS4.3 (A_G), DS5.3 (A_G), DS6.3 (A_G), J20.7
/SEG2_A: DS7.10 (A_A), DS8.10 (A_A), J20.15
/SEG2_B: DS7.9 (A_B), DS8.9 (A_B), J20.16
/SEG2_C: DS7.8 (A_C), DS8.8 (A_C), J20.17
/SEG2_D: DS7.5 (A_D), DS8.5 (A_D), J20.18
/SEG2_DP: DS7.7 (A_DP), DS8.7 (A_DP), J20.22
/SEG2_E: DS7.4 (A_E), DS8.4 (A_E), J20.19
/SEG2_F: DS7.2 (A_F), DS8.2 (A_F), J20.20
/SEG2_G: DS7.3 (A_G), DS8.3 (A_G), J20.21

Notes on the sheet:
ARC-164 plug-in LED module: six frequency digits and two preset digits
Display drivers, buffering, Teensy and backlight MOSFET are on the Power Driver Board. J20 is a 40-pin display cable.
Channel encoder removed from module. J20 contacts 25 and 26 are reserved / not connected.
Backlight LEDs and their resistors removed. J20 backlight contacts reserved for future use.
J20 DISPLAY ONLY: 40-pin 2.54mm IDC cable, 6in. Pins 1-32 retain existing assignments; 33-40 NC. Key toward PCB top edge. Label DISPLAY / J20; J10 is CONTROLS. Plain headers are not mechanically keyed.

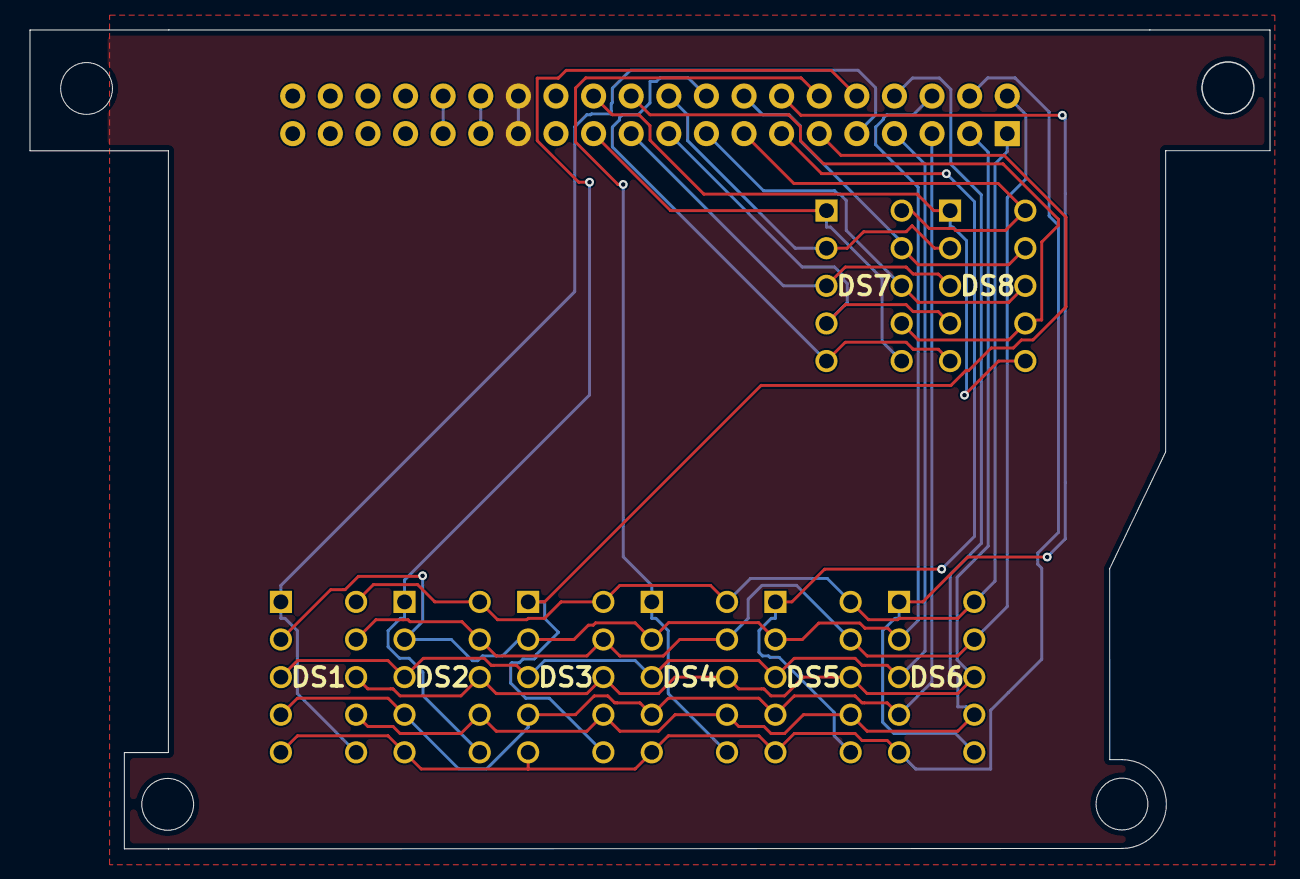
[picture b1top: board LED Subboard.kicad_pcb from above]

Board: 2 copper layers, 83.8 x 55.3 mm, 9 parts (1 on the bottom side), 27 nets.

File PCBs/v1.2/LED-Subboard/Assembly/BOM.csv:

"Refs","Value","Footprint","Qty","DNP"
"DS1","QBSLDIW301GR","ARC164_WhiteDisplays:QBSLDIW301GR","1",""
"DS2","QBSLDIW301GR","ARC164_WhiteDisplays:QBSLDIW301GR","1",""
"DS3","QBSLDIW301GR","ARC164_WhiteDisplays:QBSLDIW301GR","1",""
"DS4","QBSLDIW301GR","ARC164_WhiteDisplays:QBSLDIW301GR","1",""
"DS5","QBSLDIW301GR","ARC164_WhiteDisplays:QBSLDIW301GR","1",""
"DS6","QBSLDIW301GR","ARC164_WhiteDisplays:QBSLDIW301GR","1",""
"DS7","QBSLDIW301GR","ARC164_WhiteDisplays:QBSLDIW301GR","1",""
"DS8","QBSLDIW301GR","ARC164_WhiteDisplays:QBSLDIW301GR","1",""
"J20","TSW-120-07-L-D - DISPLAYS","Connector_PinHeader_2.54mm:PinHeader_2x20_P2.54mm_Vertical","1",""

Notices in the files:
README.md:
Licensing:
- **PCBs:** [CERN Open Hardware Licence Version 2 – Permissive (CERN-OHL-P-2.0)](https://github.com/dgdimick/ARC-164-DCS-Display/blob/main/Docs/LICENSE-CERN-OHL-P-2.0.txt)
- **Teensy firmware:** [MIT License](https://github.com/dgdimick/ARC-164-DCS-Display/blob/main/Docs/LICENSE-MIT.txt)
- **STL files:** [Creative Commons Attribution 4.0 International (CC BY 4.0)](https://github.com/dgdimick/ARC-164-DCS-Display/blob/main/Docs/LICENSE-CC-BY-4.0.txt)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
Contributing changes back is welcome, but it isn’t an extra condition of the MIT License.
